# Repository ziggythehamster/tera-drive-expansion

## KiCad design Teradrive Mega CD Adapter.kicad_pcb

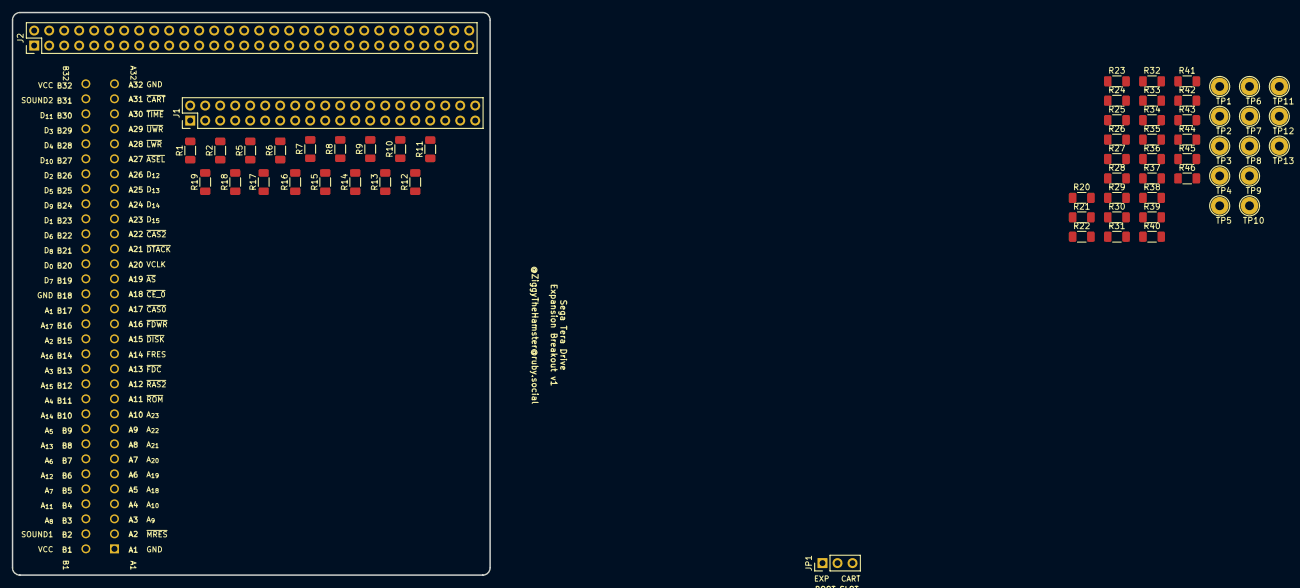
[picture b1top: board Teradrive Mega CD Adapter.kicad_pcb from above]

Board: 2 copper layers, 80.9 x 95.2 mm, 61 parts (1 on the bottom side), 103 nets, no tracks yet.

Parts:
J1: Address_Connector; PinHeader_2x20_P2.54mm_Vertical_LeftRight_Numbering
J2: Data_Control_Connector; PinHeader_2x30_P2.54mm_Vertical_LeftRight_Numbering
J5: Tera Drive Expansion Port; TE_1761469-1_BA_Numbering
JP1: Exp/Cart Boot; PinHeader_1x03_P2.54mm_Vertical
R1, R2, R5, R6, R7, R8, R9, R10, R11, R12, R13, R14, R15, R16, R17, R18, R19, R20, R21, R22, R23, R24, R25, R26, R27, R28, R29, R30, R31, R32, R33, R34, R35, R36, R37, R38, R39, R40, R41, R42, R43, R44, R45, R46: 100Ω; R_1206_3216Metric_Pad1.30x1.75mm_HandSolder
TP1: Cartridge reset (cart slot B2); TestPoint_Loop_D2.54mm_Drill1.5mm_Beaded
TP2: Cartridge chip enable (cart slot B17); TestPoint_Loop_D2.54mm_Drill1.5mm_Beaded
TP3: Cartridge address strobe (cart slot B18); TestPoint_Loop_D2.54mm_Drill1.5mm_Beaded
TP4: Cartridge 68K data clock (cart slot B19); TestPoint_Loop_D2.54mm_Drill1.5mm_Beaded
TP5: Cartridge data xfer ack (cart slot B20); TestPoint_Loop_D2.54mm_Drill1.5mm_Beaded
TP6: Cartridge ??? signal (cart slot B31); TestPoint_Loop_D2.54mm_Drill1.5mm_Beaded
TP7: Unused expansion port signal; TestPoint_Loop_D2.54mm_Drill1.5mm_Beaded
TP8: Extra address A_{18}; TestPoint_Loop_D2.54mm_Drill1.5mm_Beaded
TP9: Extra address A_{19}; TestPoint_Loop_D2.54mm_Drill1.5mm_Beaded
TP10: Extra address A_{20}; TestPoint_Loop_D2.54mm_Drill1.5mm_Beaded
TP11: Extra address A_{21}; TestPoint_Loop_D2.54mm_Drill1.5mm_Beaded
TP12: Extra address A_{22}; TestPoint_Loop_D2.54mm_Drill1.5mm_Beaded
TP13: Extra address A_{23}; TestPoint_Loop_D2.54mm_Drill1.5mm_Beaded

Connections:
AGND: J2.27 (AGND), J2.29 (AGND), J2.57 (AGND), J2.58 (AGND), J2.59 (AGND), J2.60 (AGND), R20.2, R21.2
A_{1}: J5.B17 (Pin_b17), R1.1
A_{2}: J5.B15 (Pin_b15), R2.1
A_{3}: J5.B13 (Pin_b13), R5.1
A_{4}: J5.B11 (Pin_b11), R6.1
A_{5}: J5.B9 (Pin_b9), R7.1
A_{6}: J5.B7 (Pin_b7), R8.1
A_{7}: J5.B5 (Pin_b5), R9.1
A_{8}: J5.B3 (Pin_b3), R10.1
A_{9}: J5.A3 (Pin_a3), R11.1
A_{10}: J5.A4 (Pin_a4), R12.1
A_{11}: J5.B4 (Pin_b4), R13.1
A_{12}: J5.B6 (Pin_b6), R14.1
A_{13}: J5.B8 (Pin_b8), R15.1
A_{14}: J5.B10 (Pin_b10), R16.1
A_{15}: J5.B12 (Pin_b12), R17.1
A_{16}: J5.B14 (Pin_b14), R18.1
A_{17}: J5.B16 (Pin_b16), R19.1
A_{18}: J5.A5 (Pin_a5), TP8.1
A_{19}: J5.A6 (Pin_a6), TP9.1
A_{20}: J5.A7 (Pin_a7), TP10.1
A_{21}: J5.A8 (Pin_a8), TP11.1
A_{22}: J5.A9 (Pin_a9), TP12.1
A_{23}: J5.A10 (Pin_a10), TP13.1
D_{0}: J5.B20 (Pin_b20), R22.1
D_{1}: J5.B23 (Pin_b23), R23.1
D_{2}: J5.B26 (Pin_b26), R24.1
D_{3}: J5.B29 (Pin_b29), R25.1
D_{4}: J5.B28 (Pin_b28), R26.1
D_{5}: J5.B25 (Pin_b25), R27.1
D_{6}: J5.B22 (Pin_b22), R28.1
D_{7}: J5.B19 (Pin_b19), R29.1
D_{8}: J5.B21 (Pin_b21), R30.1
D_{9}: J5.B24 (Pin_b24), R31.1
D_{10}: J5.B27 (Pin_b27), R32.1
D_{11}: J5.B30 (Pin_b30), R33.1
D_{12}: J5.A26 (Pin_a26), R34.1
D_{13}: J5.A25 (Pin_a25), R35.1
D_{14}: J5.A24 (Pin_a24), R36.1
D_{15}: J5.A23 (Pin_a23), R37.1
FRES: J5.A14 (Pin_a14), R46.1
GND: J1.18 (GND), J1.21 (GND), J1.22 (GND), J1.23 (GND), J1.24 (GND), J1.25 (GND), J1.26 (GND), J1.27 (GND), J1.28 (GND), J1.29 (GND), J1.30 (GND), J1.31 (GND), J1.32 (GND), J1.33 (GND), J1.34 (GND), J1.35 (GND), J1.36 (GND), J1.37 (GND), J1.38 (GND), J1.39 (GND), J1.40 (GND), J2.17 (GND), J2.31 (GND), J2.32 (GND), J2.33 (GND), J2.34 (GND), J2.35 (GND), J2.36 (GND), J2.37 (GND), J2.38 (GND), J2.39 (GND), J2.40 (GND), J2.41 (GND), J2.42 (GND), J2.43 (GND), J2.44 (GND), J2.45 (GND), J2.46 (GND), J2.47 (GND), J2.48 (GND), J2.49 (GND), J2.50 (GND), J2.51 (GND), J2.52 (GND), J2.53 (GND), J2.54 (GND), J2.55 (GND), J2.56 (GND), J5.A1 (Pin_a1), J5.A15 (Pin_a15), J5.A32 (Pin_a32), J5.B18 (Pin_b18), JP1.3 (B)
SL2: J2.28 (SL2), J5.B2 (Pin_b2), R20.1
SR2: J2.30 (SR2), J5.B31 (Pin_b31), R21.1
VA_{1}: J1.1 (VA_{1}), R1.2
VA_{2}: J1.3 (VA_{2}), R2.2
VA_{3}: J1.5 (VA_{3}), R5.2
VA_{4}: J1.7 (VA_{4}), R6.2
VA_{5}: J1.9 (VA_{5}), R7.2
VA_{6}: J1.11 (VA_{6}), R8.2
VA_{7}: J1.13 (VA_{7}), R9.2
VA_{8}: J1.15 (VA_{8}), R10.2
VA_{9}: J1.17 (VA_{9}), R11.2
VA_{10}: J1.16 (VA_{10}), R12.2
VA_{11}: J1.14 (VA_{11}), R13.2
VA_{12}: J1.12 (VA_{12}), R14.2
VA_{13}: J1.10 (VA_{13}), R15.2
VA_{14}: J1.8 (VA_{14}), R16.2
VA_{15}: J1.6 (VA_{15}), R17.2
VA_{16}: J1.4 (VA_{16}), R18.2
VA_{17}: J1.2 (VA_{17}), R19.2
VCC: J1.19 (VCC), J1.20 (VCC), J5.B1 (Pin_b1), J5.B32 (Pin_b32), JP1.1 (A)
VCLK: J5.A20 (Pin_a20), TP4.1
VD_{0}: J2.1 (VD_{0}), R22.2
VD_{1}: J2.3 (VD_{1}), R23.2
VD_{2}: J2.5 (VD_{2}), R24.2
VD_{3}: J2.7 (VD_{3}), R25.2
VD_{4}: J2.9 (VD_{4}), R26.2
VD_{5}: J2.11 (VD_{5}), R27.2
VD_{6}: J2.13 (VD_{6}), R28.2
VD_{7}: J2.15 (VD_{7}), R29.2
VD_{8}: J2.16 (VD_{8}), R30.2
VD_{9}: J2.14 (VD_{9}), R31.2
VD_{10}: J2.12 (VD_{10}), R32.2
VD_{11}: J2.10 (VD_{11}), R33.2
VD_{12}: J2.8 (VD_{12}), R34.2
VD_{13}: J2.6 (VD_{13}), R35.2
VD_{14}: J2.4 (VD_{14}), R36.2
VD_{15}: J2.2 (VD_{15}), R37.2
VFRES: J2.18 (~VFRES), R46.2
~ASEL: J5.A27 (Pin_a27), R41.1
~AS: J5.A19 (Pin_a19), TP3.1
~CART: J5.A31 (Pin_a31), JP1.2 (C)
~CAS0: J5.A17 (Pin_a17), R38.1
~CAS2: J5.A22 (Pin_a22), R39.1
~CE_0: J5.A18 (Pin_a18), TP2.1
~DTACK: J5.A21 (Pin_a21), TP5.1
~FDC: J5.A13 (Pin_a13), R45.1
~FDWR: J5.A16 (Pin_a16), TP7.1
~LWR: J5.A28 (Pin_a28), R42.1
~MRES: J5.A2 (Pin_a2), TP1.1
~RAS2: J5.A12 (Pin_a12), R44.1
~ROM: J5.A11 (Pin_a11), R43.1
~TIME: J5.A30 (Pin_a30), TP6.1
~UWR: J5.A29 (Pin_a29), R40.1
~VASEL: J2.21 (~VASEL), R41.2
~VCAS0: J2.19 (~VCAS0), R38.2
~VCAS2: J2.23 (~VCAS2), R39.2
~VFDC: J2.24 (~VFDC), R45.2
~VLWR: J2.26 (~VLWR), R42.2
~VRAS2: J2.25 (~VRAS2), R44.2
~VROM: J2.22 (~VROM), R43.2
~VUWR: J2.20 (~VUWR), R40.2

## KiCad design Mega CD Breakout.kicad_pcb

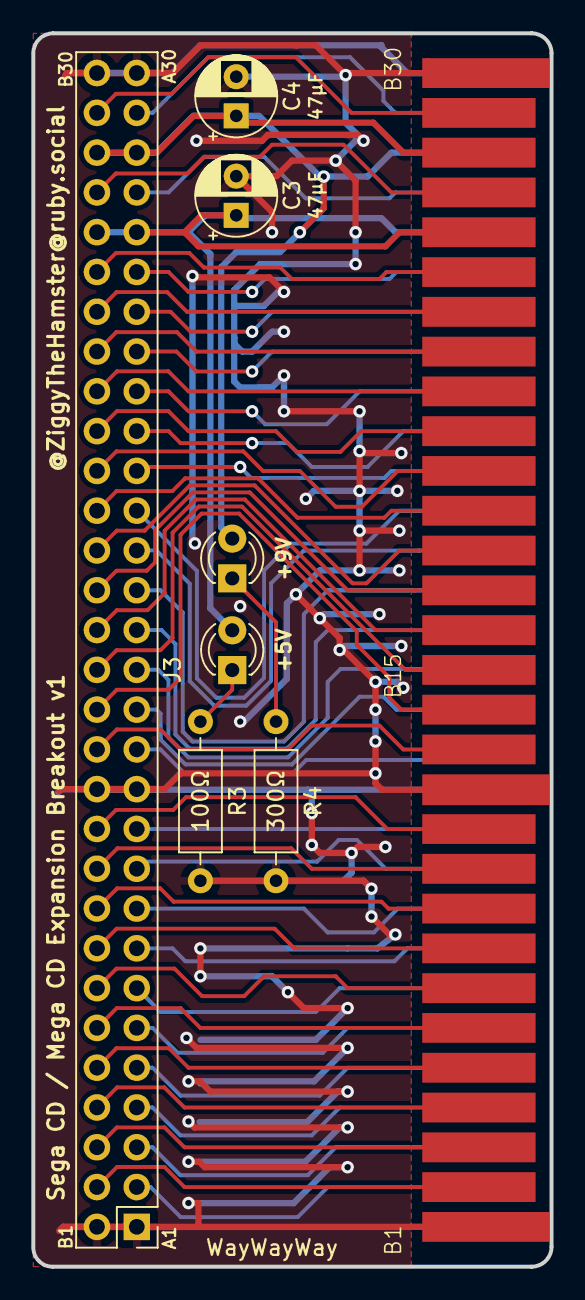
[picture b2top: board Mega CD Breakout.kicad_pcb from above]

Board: 2 copper layers, 33.1 x 78.7 mm, 8 parts (0 on the bottom side), 55 nets.

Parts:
C3, C4: 47μF; CP_Radial_D5.0mm_P2.50mm
D3: +5V Indicator; LED_D3.0mm
D4: +9V Indicator; LED_D3.0mm
J3: Mega CD Header; PinHeader_2x30_P2.54mm_Vertical_AB_Numbering
J4: Mega CD Edge Connector; MegaDrive_Exp_Edge
R3: 100Ω; R_Axial_DIN0207_L6.3mm_D2.5mm_P10.16mm_Horizontal
R4: 300Ω; R_Axial_DIN0207_L6.3mm_D2.5mm_P10.16mm_Horizontal

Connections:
+9V: C4.1, D4.2 (A), J3.A28 (Pin_a28), J3.B28 (Pin_b28), J4.A28 (Pin_a28), J4.B28 (Pin_b28)
A_{1}: J3.B3 (Pin_b3), J4.B3 (Pin_b3)
A_{2}: J3.B4 (Pin_b4), J4.B4 (Pin_b4)
A_{3}: J3.B5 (Pin_b5), J4.B5 (Pin_b5)
A_{4}: J3.B6 (Pin_b6), J4.B6 (Pin_b6)
A_{5}: J3.B7 (Pin_b7), J4.B7 (Pin_b7)
A_{6}: J3.B8 (Pin_b8), J4.B8 (Pin_b8)
A_{7}: J3.B9 (Pin_b9), J4.B9 (Pin_b9)
A_{8}: J3.B10 (Pin_b10), J4.B10 (Pin_b10)
A_{9}: J3.B11 (Pin_b11), J4.B11 (Pin_b11)
A_{10}: J3.B13 (Pin_b13), J4.B13 (Pin_b13)
A_{11}: J3.B14 (Pin_b14), J4.B14 (Pin_b14)
A_{12}: J3.B15 (Pin_b15), J4.B15 (Pin_b15)
A_{13}: J3.B16 (Pin_b16), J4.B16 (Pin_b16)
A_{14}: J3.B17 (Pin_b17), J4.B17 (Pin_b17)
A_{15}: J3.B18 (Pin_b18), J4.B18 (Pin_b18)
A_{16}: J3.B19 (Pin_b19), J4.B19 (Pin_b19)
A_{17}: J3.B20 (Pin_b20), J4.B20 (Pin_b20)
A_{18}: J3.B25 (Pin_b25), J4.B25 (Pin_b25)
A_{19}: J3.A2 (Pin_a2), J4.A2 (Pin_a2)
D_{0}: J3.A4 (Pin_a4), J4.A4 (Pin_a4)
D_{1}: J3.A5 (Pin_a5), J4.A5 (Pin_a5)
D_{2}: J3.A6 (Pin_a6), J4.A6 (Pin_a6)
D_{3}: J3.A7 (Pin_a7), J4.A7 (Pin_a7)
D_{4}: J3.A8 (Pin_a8), J4.A8 (Pin_a8)
D_{5}: J3.A9 (Pin_a9), J4.A9 (Pin_a9)
D_{6}: J3.A10 (Pin_a10), J4.A10 (Pin_a10)
D_{7}: J3.A11 (Pin_a11), J4.A11 (Pin_a11)
D_{8}: J3.A13 (Pin_a13), J4.A13 (Pin_a13)
D_{9}: J3.A14 (Pin_a14), J4.A14 (Pin_a14)
D_{10}: J3.A15 (Pin_a15), J4.A15 (Pin_a15)
D_{11}: J3.A16 (Pin_a16), J4.A16 (Pin_a16)
D_{12}: J3.A17 (Pin_a17), J4.A17 (Pin_a17)
D_{13}: J3.A18 (Pin_a18), J4.A18 (Pin_a18)
D_{14}: J3.A19 (Pin_a19), J4.A19 (Pin_a19)
D_{15}: J3.A20 (Pin_a20), J4.A20 (Pin_a20)
FRES: J3.A25 (Pin_a25), J4.A25 (Pin_a25)
GND: C3.2, C4.2, J3.A1 (Pin_a1), J3.A12 (Pin_a12), J3.A30 (Pin_a30), J3.B1 (Pin_b1), J3.B12 (Pin_b12), J3.B30 (Pin_b30), J4.A1 (Pin_a1), J4.A12 (Pin_a12), J4.A30 (Pin_a30), J4.B1 (Pin_b1), J4.B12 (Pin_b12), J4.B30 (Pin_b30), R3.2, R4.2
unnamed: D3.1 (K), R3.1
unnamed: D4.1 (K), R4.1
SL2: J3.B29 (Pin_b29), J4.B29 (Pin_b29)
SL3: J3.B27 (Pin_b27), J4.B27 (Pin_b27)
SR2: J3.A29 (Pin_a29), J4.A29 (Pin_a29)
SR3: J3.A27 (Pin_a27), J4.A27 (Pin_a27)
VCC: C3.1, D3.2 (A), J3.A26 (Pin_a26), J3.B26 (Pin_b26), J4.A26 (Pin_a26), J4.B26 (Pin_b26)
~ASEL: J3.A22 (Pin_a22), J4.A22 (Pin_a22)
~CAS0: J3.A3 (Pin_a3), J4.A3 (Pin_a3)
~CAS2: J3.B23 (Pin_b23), J4.B23 (Pin_b23)
~DISK: J3.B2 (Pin_b2), J4.B2 (Pin_b2)
~FDC: J3.A24 (Pin_a24), J4.A24 (Pin_a24)
~FDWR: J3.B24 (Pin_b24), J4.B24 (Pin_b24)
~LWR: J3.B21 (Pin_b21), J4.B21 (Pin_b21)
~RAS2: J3.A23 (Pin_a23), J4.A23 (Pin_a23)
~ROM: J3.A21 (Pin_a21), J4.A21 (Pin_a21)
~UWR: J3.B22 (Pin_b22), J4.B22 (Pin_b22)

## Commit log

2024-05-13 Root commit.
2024-05-13 Add license and gitignore
2024-05-13 Add v1 gerbers
2024-05-13 Add Sega footprint library
2024-05-13 Add digikey footprints
2024-05-13 Add tables
2024-05-13 Add the rest of the stuff
2024-08-19 Work on v2
